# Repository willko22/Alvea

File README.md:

# ⬡ Alvea

**Wireless split keyboard · nRF52840 · ZMK · hexagonal keycaps**

A low-power, battery-powered wireless split keyboard. Each half is a fully independent BLE device with its own battery, per-key LEDs, and USB-C charging.

> [!WARNING]
> **Work in progress — nothing here has been fabricated or tested yet.**
> The hardware is fully designed, but the boards haven't been manufactured, assembled, or brought up. Any performance numbers are design targets, not measurements, and the firmware doesn't exist yet. This repo is documentation of my hobby build, not a guide for replicating it.

---

## 🗺️ Roadmap

| Stage | Status |
|-------|--------|
| Schematic design | ✅ Done |
| PCB layout | ✅ Done |
| BOM finalized | ✅ Done |
| **PCB polishing + panelization** | 🔄 **In progress** |
| PCB fabrication (JLCPCB) | ⬜ Planned |
| SMT assembly | ⬜ Planned |
| Hand-soldering (sockets, LEDs, battery lead) | ⬜ Planned |
| Bootloader flashing (SWD, one-time) | ⬜ Planned |
| ZMK firmware (keymap + board definition) | ⬜ Not started |
| Bring-up & testing | ⬜ Planned |
| 3D-printed case | ⬜ Planned (after electronics work) |
| Renders / photos | ⬜ Not yet available |

**Right now:** finishing the PCBs and panelizing for fabrication.
**After that:** fabrication → SMT assembly → hand-soldering → firmware → testing → case design.

Legend: ✅ done · 🔄 in progress · ⬜ planned / not started

---

## ✨ Highlights

- **Wireless BLE** — each half is fully independent; no TRRS cable between halves
- **nRF52840 module (Ebyte E73-2G4M08S1C)** — integrated PCB antenna, so no RF design needed
- **ZMK firmware** *(planned)* — flexible keymaps, deep-sleep power management, drag-and-drop USB updates
- **19 functional keys per half** in a 5×4 matrix, plus a dedicated power switch
- **Per-key LEDs** shining up through translucent hexagonal HEX keycaps
- **USB-C charging** with a dedicated fuel gauge for accurate battery reporting
- **Single 3.5 Ah LiPo per half** with ZMK deep sleep — see [`DESIGN.md`](DESIGN.md) for the per-component power breakdown

Full technical detail — every component, net, pin assignment, BOM line, the power/charging architecture, and the design rationale — lives in [`DESIGN.md`](DESIGN.md).

---

## 🛒 Sourcing

| Source | Parts |
|--------|-------|
| [JLCPCB](https://jlcpcb.com/) | PCB fabrication + SMT assembly of the small components |
| [Keeb Supply](https://keeb.supply/) | Twilight low-profile switches, HEX keycaps, foam Choc spacers, hotswap Choc sockets, battery connector |
| [TME](https://www.tme.eu/) | Per-key LEDs, battery, and a Raspberry Pi Pico (firmware burner + SWD debugger) |

The switches are **not soldered** — only the hotswap Choc sockets are, and the switches snap into those.

---

## 📄 License

This repository is **split-licensed**:

- **Hardware design files & documentation** — [CC BY-NC 4.0](https://creativecommons.org/licenses/by-nc/4.0/). Use, share, and modify freely with credit, but **not for commercial purposes** — no one may sell Alvea or its derivatives without my explicit consent. See [`LICENSE`](LICENSE).
- **Firmware** (ZMK keymap / board definition) — [MIT](https://opensource.org/licenses/MIT), matching [ZMK](https://zmk.dev/)'s own license so it stays compatible with the ZMK ecosystem. See [`LICENSE-FIRMWARE`](LICENSE-FIRMWARE).

The non-commercial restriction protects the hardware — the part someone would actually manufacture. The firmware is a thin config on top of MIT-licensed ZMK, so it matches ZMK.

---

## 🙏 Acknowledgements

- [ZMK Firmware](https://zmk.dev/)
- [Adafruit nRF52 Bootloader](https://github.com/adafruit/Adafruit_nRF52_Bootloader)
- [fkcaps HEX keycaps](https://fkcaps.com/keycaps/hex) by *s-ol*
- The KiCad community for guidance

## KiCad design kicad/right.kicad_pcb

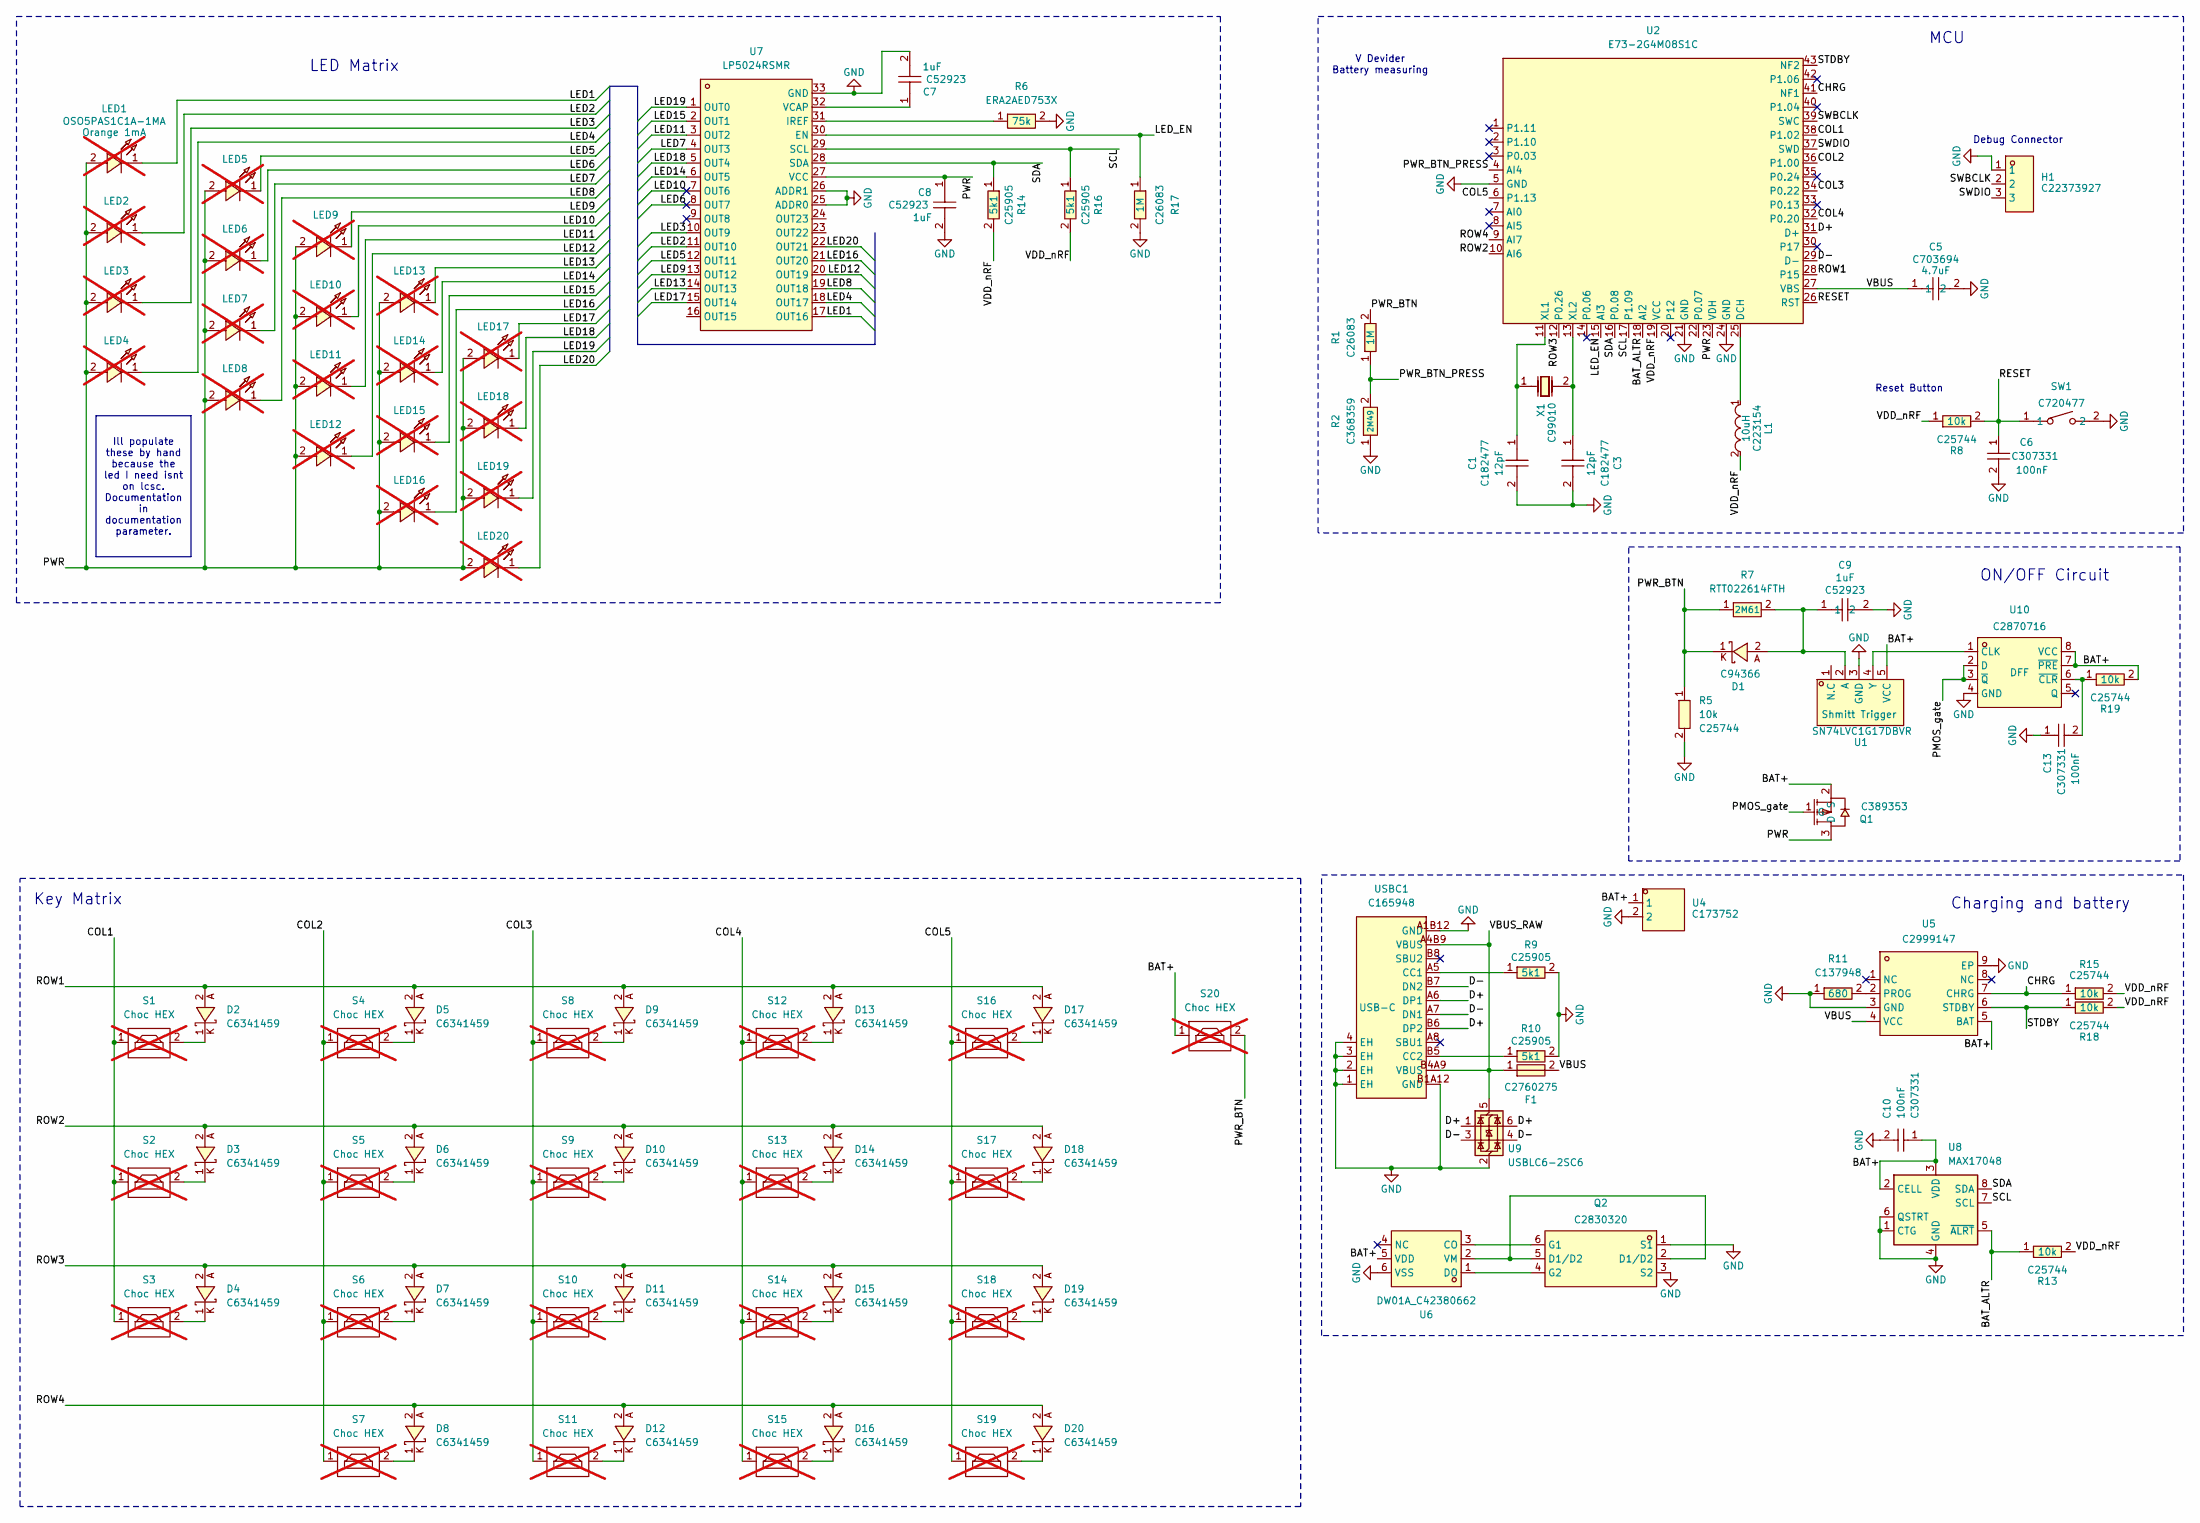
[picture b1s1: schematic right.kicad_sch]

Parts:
C1, C3: 0402CG120F500NT; C0402; LCSC Part C182477
C5: ZRB15XR61A475KE01D; C0402; MPN ZRB15XR61A475KE01D; LCSC Part C703694
C6, C10, C13: CL05B104KB54PNC; C0402; LCSC Part C307331
C7, C8, C9: CL05A105KA5NQNC; C0402; LCSC Part C52923
D1: NSR05F20NXT5G; DSN2_L1.0-W0.6-RD; LCSC Part C94366
D2, D3, D4, D5, D6, D7, D8, D9, D10, D11, D12, D13, D14, D15, D16, D17, D18, D19, D20: CDSQC4148-HF; X1-DFN1006-2_L1.0-W0.6-RD; LCSC Part C6341459
F1: SMD1206-150C-16V; F1206; LCSC Part C2760275
H1: HC-PM254-8.5H-1X3PW; HDR-TH_3P-P2.54_HC-PM254-8.5H-1X3PW; LCSC Part C22373927
L1: BRC2016T100K; IND-SMD_L2.0-W1.6_BRC2016; LCSC Part C223154
LED1, LED2, LED3, LED4, LED5, LED6, LED7, LED8, LED9, LED10, LED11, LED12, LED13, LED14, LED15, LED16, LED17, LED18, LED19, LED20: OSO5PAS1C1A-1MA; LED-SMD_L3.2-W2.8-LS3.5-RD-BLUE; LCSC Part OSO5PAS1C1A-1MA -> on tme.ue; not fitted
Q1: PMF170XP,115; SOT-323-3_L2.0-W1.3-P1.30-LS2.1-BR; LCSC Part C389353
Q2: FS8205A_C2830320; SOT-23-6_L2.9-W1.6-P0.95-LS2.8-BR; LCSC Part C2830320
R1, R17: 0402WGF1004TCE; R0402; LCSC Part C26083
R2: WR04W2494FTL; R0402; LCSC Part C368359
R5, R8, R13, R15, R18, R19: 0402WGF1002TCE; R0402; LCSC Part C25744
R6: ERA2AED753X; R0402; MPN ERA2AED753X; LCSC Part C491105
R7: RTT022614FTH; R0402; MPN RTT022614FTH; LCSC Part C166493
R9, R10, R14, R16: 0402WGF5101TCE; R0402; LCSC Part C25905
R11: RC0402FR-07680RL; R0402; LCSC Part C137948
S1, S2, S3, S4, S5, S6, S7, S8, S9, S10, S11, S12, S13, S14, S15, S16, S17, S18, S19, S20: Choc HEX; PG1350_hotswap; not fitted
SW1: TS-1088-AR02016; SW-SMD_L3.9-W3.0-P4.45; LCSC Part C720477
U1: SN74LVC1G17DBVR; SOT-23-5_L3.0-W1.7-P0.95-LS2.8-BR; MPN SN74LVC1G17DBVR; LCSC Part C7836
U2: E73-2G4M08S1C; WIRELM-SMD_E73-2G4M08S1C; LCSC Part C356849
U4: S2B-PH-K-S(LF)(SN); CONN-TH_S2B-PH-K-S-LF-SN; LCSC Part C173752
U5: BL8573CS8TR; ESOP-8_L4.9-W3.9-P1.27-LS6.0-BL-EP; LCSC Part C2999147
U6: DW01A_C42380662; SOT-23-6_L2.9-W1.6-P0.95-LS2.9-BL; LCSC Part C42380662
U7: LP5024RSMR; VQFN-32_L4.0-W4.0-P0.40-TL-EP; LCSC Part C427525
U8: MAX17048; DFN-8_2x2mm_P0.5mm_EP1.2x0.8mm; LCSC Part C2682616
U9: USBLC6-2SC6; SOT-23-6
U10: SN74LVC1G74DQER; X2SON-8_L1.4-W1.0-P0.35-BL; LCSC Part C2870716
USBC1: TYPE-C-31-M-12; USB-C_SMD-TYPE-C-31-M-12_1; LCSC Part C165948
X1: FC-13532.768KHZ9PF20PPM; OSC-SMD_L3.2-W1.5; LCSC Part C99010

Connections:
/BAT+: C10.1, Q1.2 (S), R19.2, S20.1, U1.5 (VCC), U4.1, U5.5 (BAT), U6.5 (VDD), U8.2 (CELL), U8.3 (VDD), U10.7 (~PRE), U10.8 (VCC); also elsewhere on the board
/BAT_ALTR: R13.1, U2.18 (AI2), U8.5 (~ALRT)
/CHRG: R15.1, U2.41 (NF1), U5.7 (CHRG)
/COL1: S1.1, S2.1, S3.1, U2.38 (P1.02)
/COL2: S4.1, S5.1, S6.1, S7.1, U2.36 (P1.00)
/COL3: S8.1, S9.1, S10.1, S11.1, U2.34 (P0.22)
/COL4: S12.1, S13.1, S14.1, S15.1, U2.32 (P0.20)
/COL5: S16.1, S17.1, S18.1, S19.1, U2.6 (P1.13)
/D+: U2.31 (D+), U9.1 (I/O1), U9.6 (I/O1), USBC1.A6 (DP1), USBC1.B6 (DP2)
/D-: U2.29 (D-), U9.3 (I/O2), U9.4 (I/O2), USBC1.A7 (DN1), USBC1.B7 (DN2)
/LED1: LED1.1, U7.17 (OUT16)
/LED2: LED2.1, U7.11 (OUT10)
/LED3: LED3.1, U7.10 (OUT9)
/LED4: LED4.1, U7.18 (OUT17)
/LED5: LED5.1, U7.12 (OUT11)
/LED6: LED6.1, U7.8 (OUT7)
/LED7: LED7.1, U7.4 (OUT3)
/LED8: LED8.1, U7.19 (OUT18)
/LED9: LED9.1, U7.13 (OUT12)
/LED10: LED10.1, U7.7 (OUT6)
/LED11: LED11.1, U7.3 (OUT2)
/LED12: LED12.1, U7.20 (OUT19)
/LED13: LED13.1, U7.14 (OUT13)
/LED14: LED14.1, U7.6 (OUT5)
/LED15: LED15.1, U7.2 (OUT1)
/LED16: LED16.1, U7.21 (OUT20)
/LED17: LED17.1, U7.15 (OUT14)
/LED18: LED18.1, U7.5 (OUT4)
/LED19: LED19.1, U7.1 (OUT0)
/LED20: LED20.1, U7.22 (OUT21)
/LED_EN: R17.1, U2.15 (AI3), U7.30 (EN)
/PMOS_gate: Q1.1 (G), U10.2 (D), U10.3 (~Q)
/PWR: C8.1, LED1.2, LED2.2, LED3.2, LED4.2, LED5.2, LED6.2, LED7.2, LED8.2, LED9.2, LED10.2, LED11.2, LED12.2, LED13.2, LED14.2, LED15.2, LED16.2, LED17.2, LED18.2, LED19.2, LED20.2, Q1.3 (D), U2.23 (VDH), U7.27 (VCC); also elsewhere on the board
/PWR_BTN: D1.1, R1.2, R5.1, R7.1, S20.2
/PWR_BTN_PRESS: R1.1, R2.2, U2.4 (AI4)
/RESET: C6.1, R8.2, SW1.1, U2.26 (RST)
/ROW1: D2.2, D5.2, D9.2, D13.2, D17.2, U2.28 (P15)
/ROW2: D3.2, D6.2, D10.2, D14.2, D18.2, U2.10 (AI6)
/ROW3: D4.2, D7.2, D11.2, D15.2, D19.2, U2.12 (P0.26)
/ROW4: D8.2, D12.2, D16.2, D20.2, U2.9 (AI7)
/SCL: R16.1, U2.17 (P1.09), U7.29 (SCL), U8.7 (SCL)
/SDA: R14.1, U2.16 (P0.08), U7.28 (SDA), U8.8 (SDA)
/STDBY: R18.1, U2.43 (NF2), U5.6 (STDBY)
/SWBCLK: H1.2, U2.39 (SWC)
/SWDIO: H1.3, U2.37 (SWD)
/VBUS: C5.1, F1.2, U2.27 (VBS), U5.4 (VCC); also elsewhere on the board
/VBUS_RAW: F1.1, U9.5 (VBUS), USBC1.A4B9 (VBUS), USBC1.B4A9 (VBUS)
/VDD_nRF: L1.2, R8.1, R13.2, R14.2, R15.2, R16.2, R18.2, U2.19 (VCC); also elsewhere on the board
GND: C1.2, C3.2, C5.2, C6.2, C7.2, C8.2, C9.2, C10.2, C13.1, H1.1, Q2.1 (S1), Q2.3 (S2), R2.1, R5.2, R6.2, R9.2, R10.2, R11.1, R17.2, SW1.2, U1.3 (GND), U2.5 (GND), U2.21 (GND), U2.24 (GND), U4.2, U5.3 (GND), U5.9 (EP), U6.6 (VSS), U7.25 (ADDR0), U7.26 (ADDR1), U7.33 (GND), U8.1 (CTG), U8.4 (GND), U8.6 (QSTRT), U8.9 (GND), U9.2 (GND), U10.4 (GND), USBC1.1 (EH), USBC1.2 (EH), USBC1.3 (EH), USBC1.4 (EH), USBC1.A1B12 (GND), USBC1.B1A12 (GND); also elsewhere on the board
unnamed: D2.1, S1.2
unnamed: D3.1, S2.2
unnamed: D4.1, S3.2
unnamed: D5.1, S4.2
unnamed: D6.1, S5.2
unnamed: D7.1, S6.2
unnamed: D8.1, S7.2
unnamed: D9.1, S8.2
unnamed: D10.1, S9.2
unnamed: D11.1, S10.2
unnamed: D12.1, S11.2
unnamed: D13.1, S12.2
unnamed: D14.1, S13.2
unnamed: D15.1, S14.2
unnamed: D16.1, S15.2
unnamed: D17.1, S16.2
unnamed: D18.1, S17.2
unnamed: D19.1, S18.2
unnamed: D20.1, S19.2
unnamed: Q2.6 (G1), U6.3 (CO)
unnamed: Q2.4 (G2), U6.1 (DO)
unnamed: C9.1, D1.2, R7.2, U1.2 (A)
unnamed: U1.4 (Y), U10.1 (CLK)
unnamed: L1.1, U2.25 (DCH)
unnamed: C1.1, U2.11 (XL1), X1.1
unnamed: C3.1, U2.13 (XL2), X1.2
unnamed: R11.2, U5.2 (PROG)
unnamed: Q2.2 (D1/D2), Q2.5 (D1/D2), U6.2 (VM)
unnamed: R6.1, U7.31 (IREF)
unnamed: C7.1, U7.32 (VCAP)
unnamed: C13.2, R19.1, U10.6 (~CLR)
unnamed: R9.1, USBC1.A5 (CC1)
unnamed: R10.1, USBC1.B5 (CC2)

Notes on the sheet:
Charging and battery
MCU
Debug Connector
ON/OFF Circuit
Reset Button
Key Matrix
V Devider Battery measuring
LED Matrix
Ill populate these by hand because the led I need isnt on lcsc. Documentation in documentation parameter.

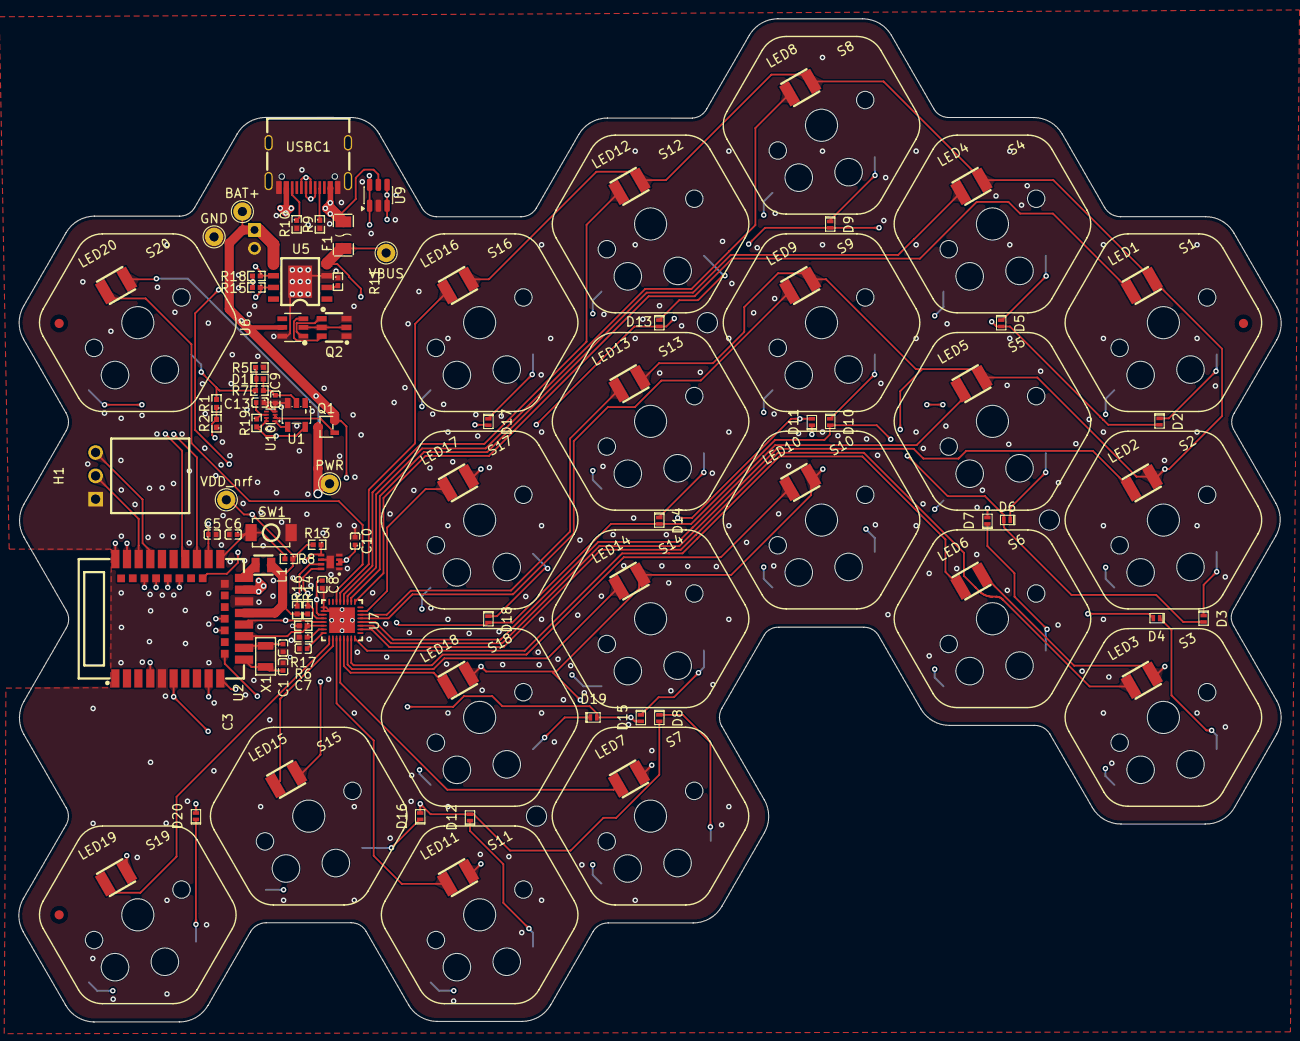
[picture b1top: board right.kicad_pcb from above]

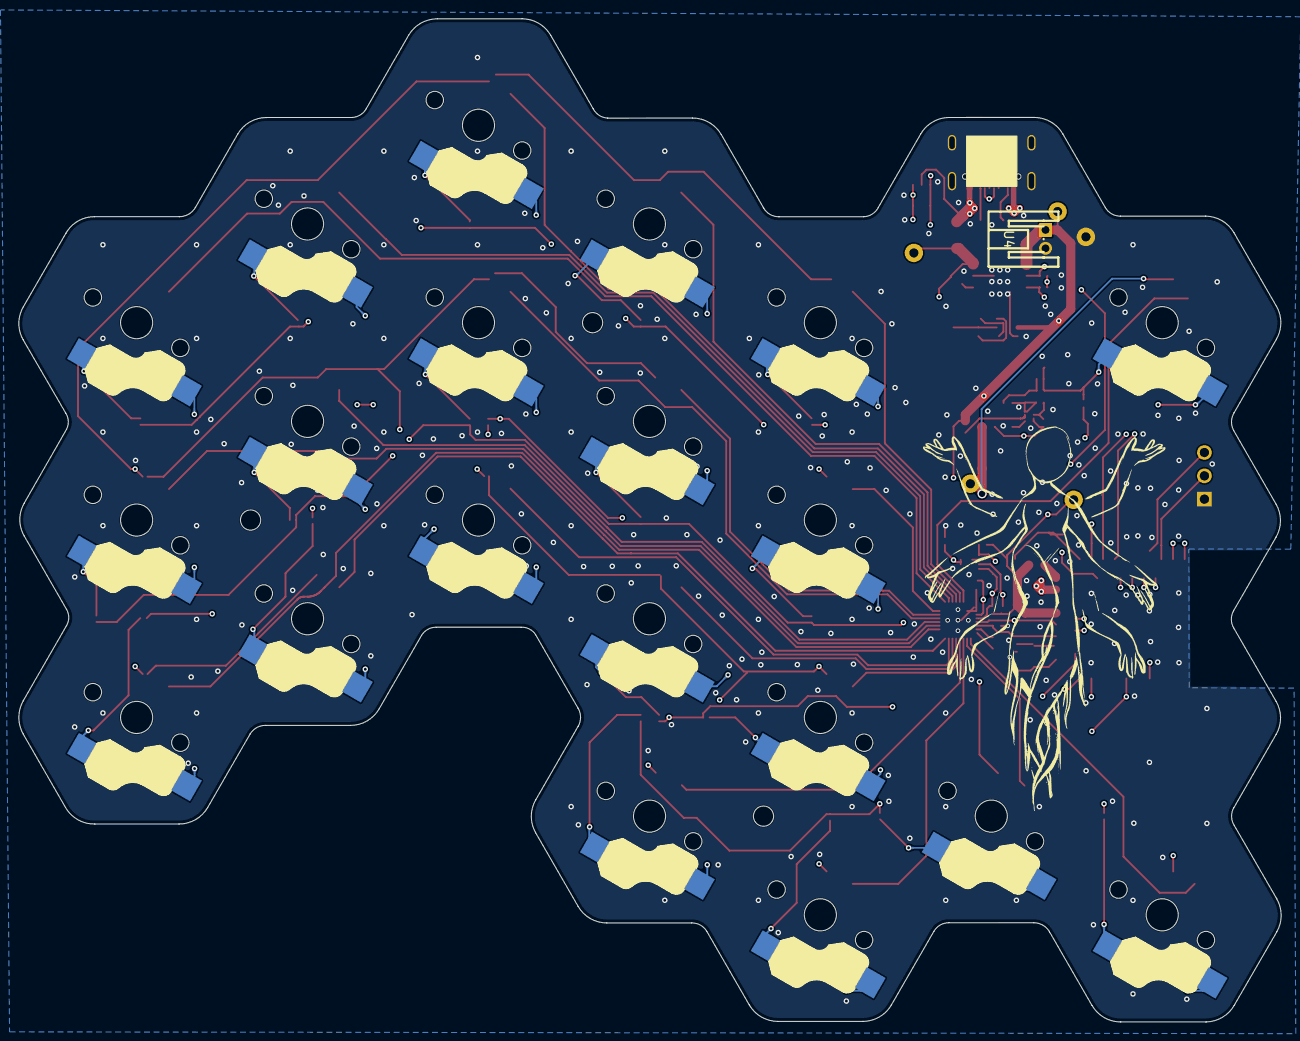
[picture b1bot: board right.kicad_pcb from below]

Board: 4 copper layers, 137.5 x 109.3 mm, 111 parts (22 on the bottom side), 82 nets.

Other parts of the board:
BAT+: TestPoint_THTPad_D2.0mm_Drill1.0mm
Fi4, Fi5: Fiducial_1mm_Mask2mm
Fi6: Fiducial_1mm_Mask2mm
G**: LOGO; handy
GND: TestPoint_THTPad_D2.0mm_Drill1.0mm
PWR: TestPoint_THTPad_D2.0mm_Drill1.0mm
VBUS: TestPoint_THTPad_D2.0mm_Drill1.0mm
VDD_nrf: TestPoint_THTPad_D2.0mm_Drill1.0mm

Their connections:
/BAT+: BAT+.1; also elsewhere on the board
/PWR: PWR.1; also elsewhere on the board
/VBUS: VBUS.1; also elsewhere on the board
/VDD_nRF: VDD_nrf.1; also elsewhere on the board
GND: GND.1; also elsewhere on the board

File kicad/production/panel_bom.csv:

Designator,Footprint,Quantity,Value,LCSC Part #
"C1_2, C3_2",C0402,2,0402CG120J500NT,C1547
"C1, C3",C0402,2,0402CG120F500NT,C182477
"C10, C13, C4, C6_2, C6, C9_2",C0402,6,CL05B104KB54PNC,C307331
"C2, C7_2, C7, C8_2, C8, C9",C0402,6,CL05A105KA5NQNC,C52923
"C5_2, C5",C0402,2,ZRB15XR61A475KE01D,C703694
"D1_2, D1",DSN2_L1.0-W0.6-RD,2,NSR05F20NXT5G,C94366
"D10_2, D10, D11_2, D11, D12_2, D12, D13_2, D13, D14_2, D14, D15_2, D15, D16_2, D16, D17_2, D17, D18_2, D18, D19_2, D19, D2_2, D2, D20_2, D20, D3_2, D3, D4_2, D4, D5_2, D5, D6_2, D6, D7_2, D7, D8_2, D8, D9_2, D9",X1-DFN1006-2_L1.0-W0.6-RD,38,CDSQC4148-HF,C6341459
"F1_2, F1",F1206,2,SMD1206-150C-16V,C2760275
"FI1, FI2, FI3, FI6",,4,Fiducial_1mm_Mask2mm,
H1_2,HDR-TH_3P-P2.54_HC-PM254-8.5H-1X3PW,1,HC-PM254-8.5H-1X3PW,C22373927
L1_2,IND-SMD_L2.0-W1.6_BRC2016,1,BRC2016T100K,C223154
"Q1_2, Q1",SOT-323-3_L2.0-W1.3-P1.30-LS2.1-BR,2,"PMF170XP,115",C389353
"Q2_2, Q2",SOT-23-6_L2.9-W1.6-P0.95-LS2.8-BR,2,FS8205A_C2830320,C2830320
"R1_2, R1, R17_2, R17",R0402,4,0402WGF1004TCE,C26083
"R10_2, R10, R14_2, R14, R16_2, R16, R9_2, R9",R0402,8,0402WGF5101TCE,C25905
"R11_2, R11",R0402,2,RC0402FR-07680RL,C137948
"R12, R13_2, R13, R15, R18, R19, R3, R4, R5, R7_2, R8_2, R8",R0402,12,0402WGF1002TCE,C25744
"R2_2, R2",R0402,2,WR04W2494FTL,C368359
"R5_2, R7",R0402,2,RTT022614FTH,C166493
"R6_2, R6",R0402,2,ERA2AED753X,C491105
"SW1_2, SW1",SW-SMD_L3.9-W3.0-P4.45,2,TS-1088-AR02016,C720477
"U1_2, U1",SOT-23-5_L3.0-W1.7-P0.95-LS2.8-BR,2,SN74LVC1G17DBVR,C7836
U10,X2SON-8_L1.4-W1.0-P0.35-BL,1,SN74LVC1G74DQER,C2870716
U2_2,WIRELM-SMD_E73-2G4M08S1C,1,E73-2G4M08S1C,C356849
U4_2,CONN-TH_S2B-PH-K-S-LF-SN,1,S2B-PH-K-S(LF)(SN),C173752
"U5_2, U5",ESOP-8_L4.9-W3.9-P1.27-LS6.0-BL-EP,2,BL8573CS8TR,C2999147
U6_2,SOT-23-6_L2.9-W1.6-P0.95-LS2.9-BL,1,DW01A_C42380662,C42380662
U7_2,VQFN-32_L4.0-W4.0-P0.40-TL-EP,1,LP5024RSMR,C427525
"U8_2, U8",DFN-8_2x2mm_P0.5mm_EP1.2x0.8mm,2,MAX17048,C2682616
"U9_2, U9",SOT-23-6,2,USBLC6-2SC6,
"USBC1_2, USBC1",USB-C_SMD-TYPE-C-31-M-12_1,2,TYPE-C-31-M-12,C165948
"X1_2, X1",OSC-SMD_L3.2-W1.5,2,FC-13532.768KHZ9PF20PPM,C99010

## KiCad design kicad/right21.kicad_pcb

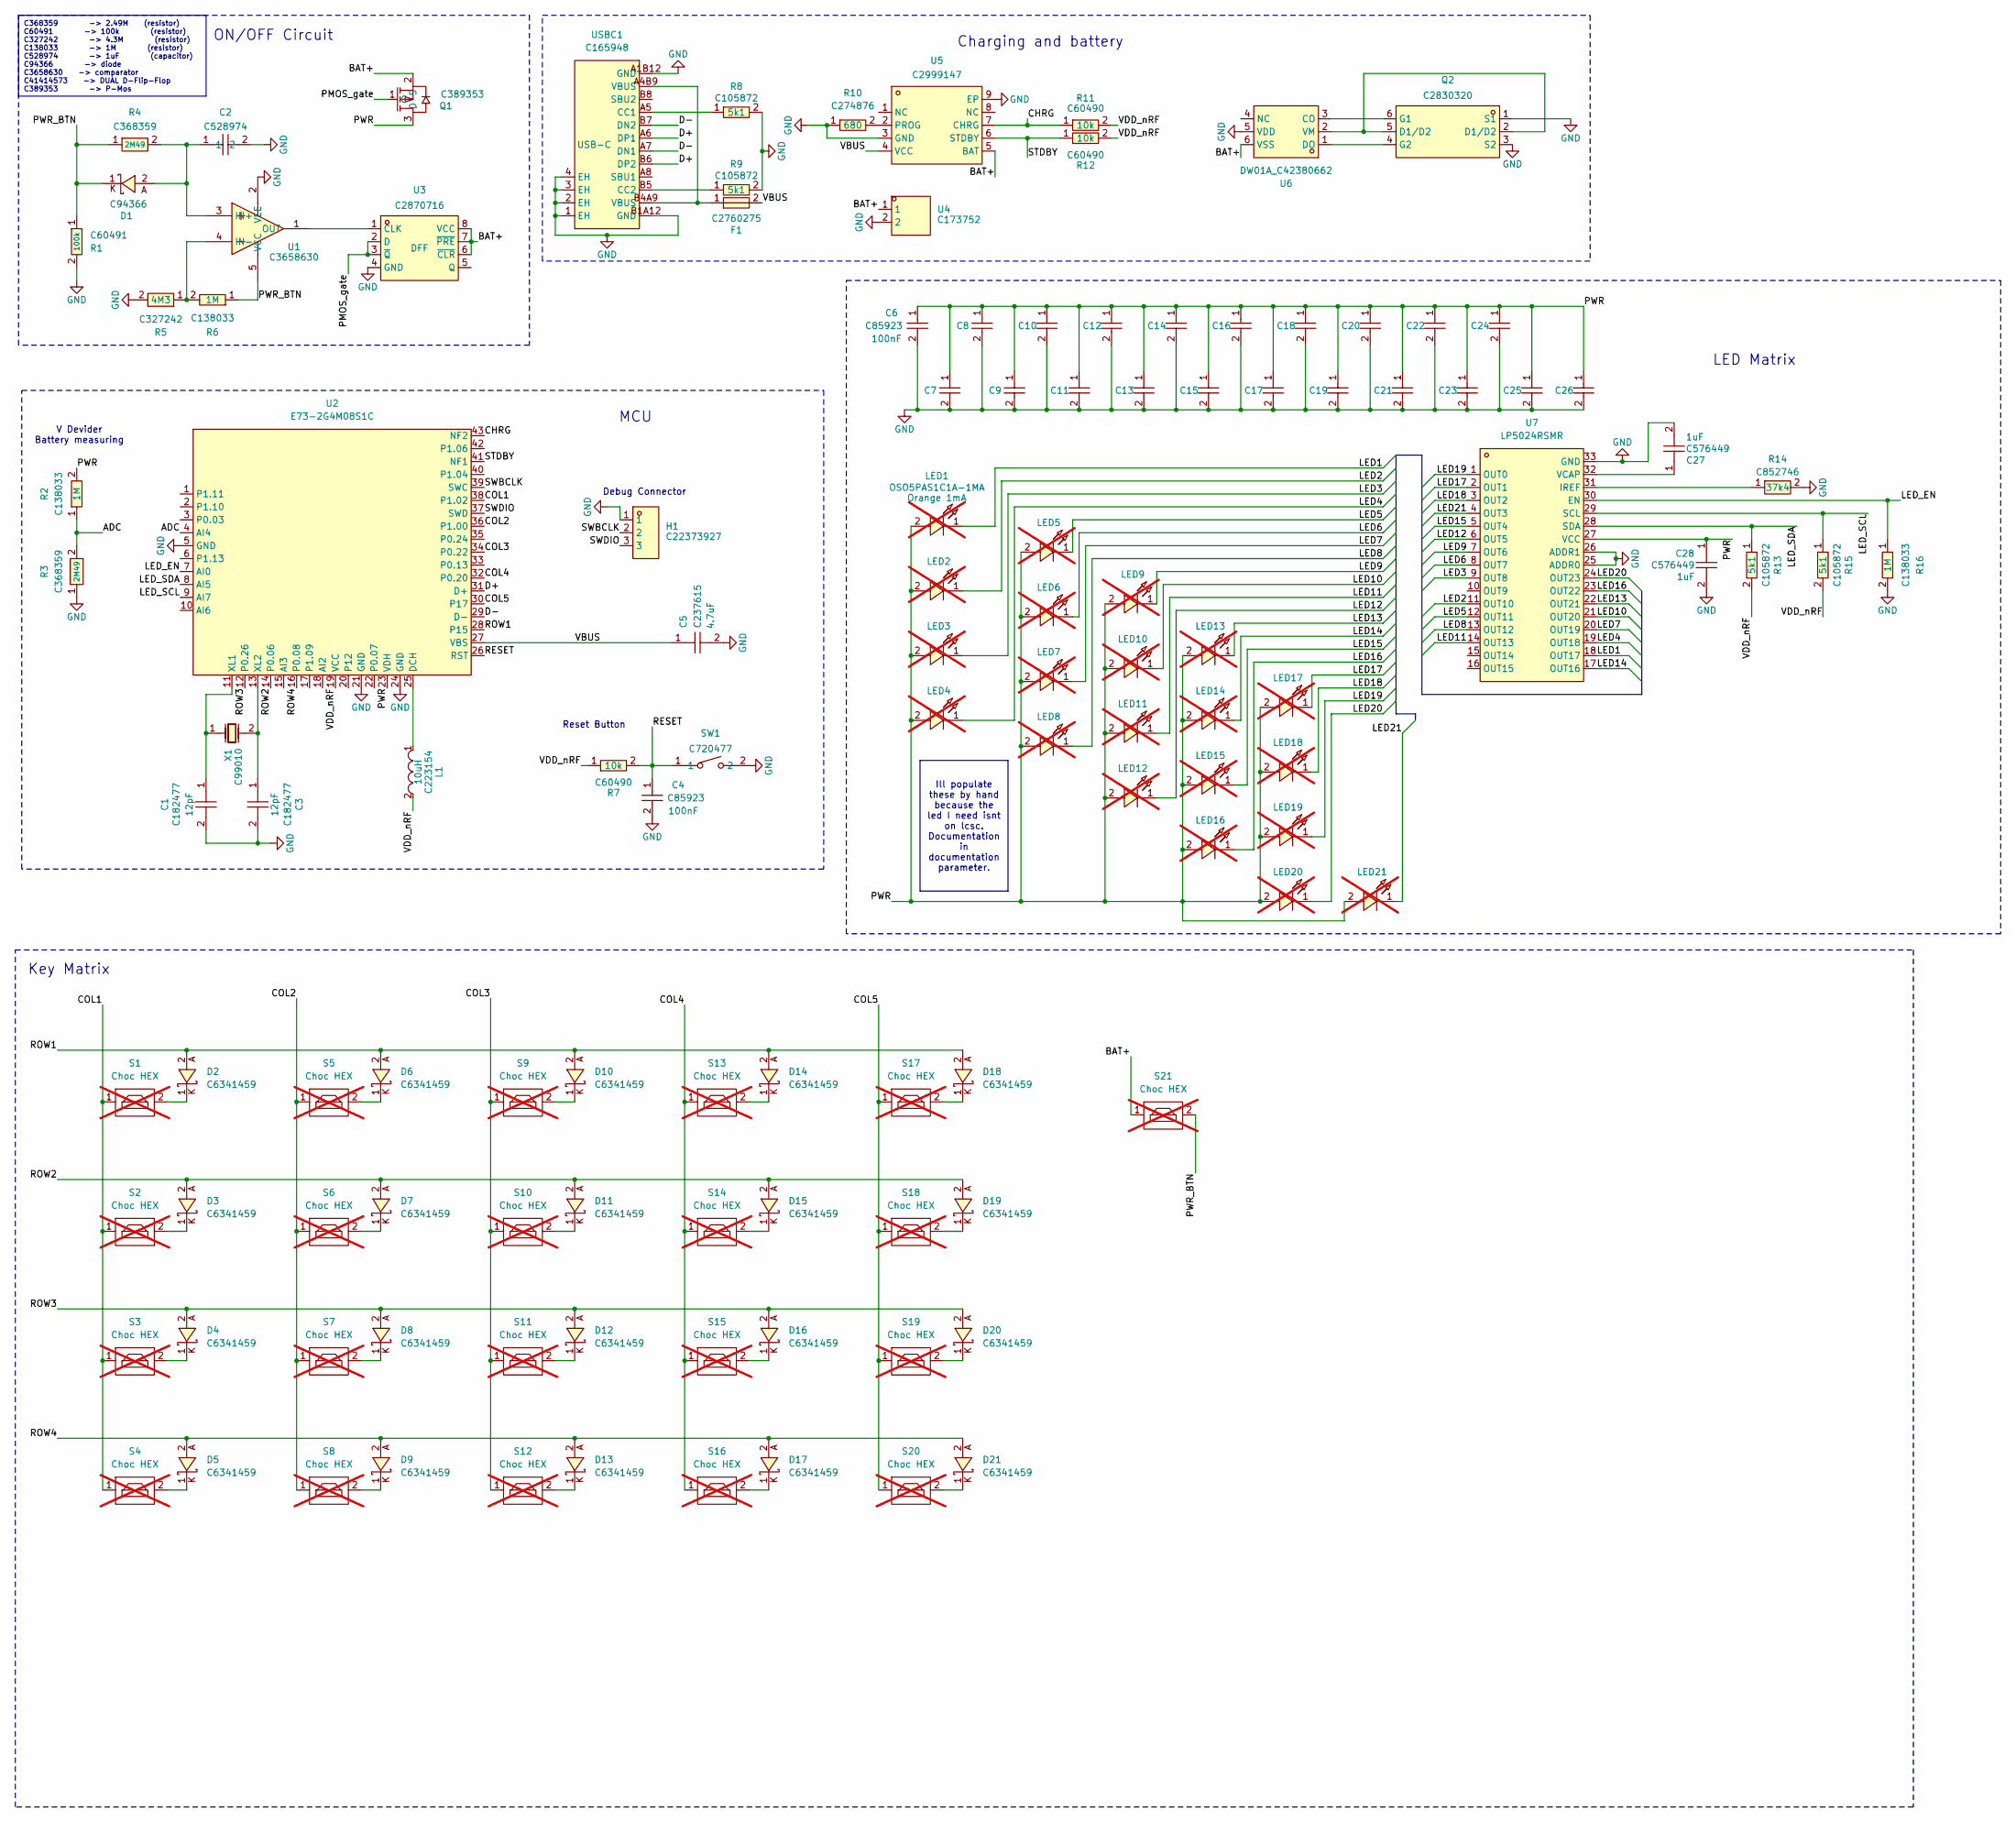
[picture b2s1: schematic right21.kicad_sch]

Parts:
C1, C3: 0402CG120F500NT; C0402; LCSC Part C182477
C2: GRM155Z71A105KE01D; C0402; LCSC Part C528974
C4, C6, C7, C8, C9, C10, C11, C12, C13, C14, C15, C16, C17, C18, C19, C20, C21, C22, C23, C24, C25, C26: GRM033C71C104KE14D; C0201; LCSC Part C85923
C5: GRM188C71C475KE21D; C0603; LCSC Part C237615
C27, C28: GRM155C71C105KE11D; C0402; LCSC Part C576449
D1: NSR05F20NXT5G; DSN2_L1.0-W0.6-RD; LCSC Part C94366
D2, D3, D4, D5, D6, D7, D8, D9, D10, D11, D12, D13, D14, D15, D16, D17, D18, D19, D20, D21: CDSQC4148-HF; X1-DFN1006-2_L1.0-W0.6-RD; LCSC Part C6341459
F1: SMD1206-150C-16V; F1206; LCSC Part C2760275
H1: HC-PM254-8.5H-1X3PW; HDR-TH_3P-P2.54_HC-PM254-8.5H-1X3PW; LCSC Part C22373927
L1: BRC2016T100K; IND-SMD_L2.0-W1.6_BRC2016; LCSC Part C223154
LED1, LED2, LED3, LED4, LED5, LED6, LED7, LED8, LED9, LED10, LED11, LED12, LED13, LED14, LED15, LED16, LED17, LED18, LED19, LED20, LED21: OSO5PAS1C1A-1MA; LED-SMD_L3.2-W2.8-LS3.5-RD-BLUE; LCSC Part OSO5PAS1C1A-1MA -> on tme.ue; not fitted
Q1: PMF170XP,115; SOT-323-3_L2.0-W1.3-P1.30-LS2.1-BR; LCSC Part C389353
Q2: FS8205A_C2830320; SOT-23-6_L2.9-W1.6-P0.95-LS2.8-BR; LCSC Part C2830320
R1: RC0402FR-07100KL; R0402; LCSC Part C60491
R2, R6, R16: RC0402FR-071ML; R0402; LCSC Part C138033
R3, R4: WR04W2494FTL; R0402; LCSC Part C368359
R5: RC0402FR-074M3L; R0402; LCSC Part C327242
R7, R11, R12: RC0402FR-0710KL; R0402; LCSC Part C60490
R8, R9, R13, R15: RC0402FR-075K1L; R0402; LCSC Part C105872
R10: RC0201FR-07680RL; R0201; LCSC Part C274876
R14: RT0402BRD0737K4L; R0402; LCSC Part C852746
S1, S2, S3, S4, S5, S6, S7, S8, S9, S10, S11, S12, S13, S14, S15, S16, S17, S18, S19, S20, S21: Choc HEX; PG1350_hotswap; not fitted
SW1: TS-1088-AR02016; SW-SMD_L3.9-W3.0-P4.45; LCSC Part C720477
U1: TLV7031QDCKRQ1; SC-70-5_L2.0-W1.3-P0.65-LS2.1-BR; LCSC Part C3658630
U2: E73-2G4M08S1C; WIRELM-SMD_E73-2G4M08S1C; LCSC Part C356849
U3: SN74LVC1G74DQER; X2SON-8_L1.4-W1.0-P0.35-BL; LCSC Part C2870716
U4: S2B-PH-K-S(LF)(SN); CONN-TH_S2B-PH-K-S-LF-SN; LCSC Part C173752
U5: BL8573CS8TR; ESOP-8_L4.9-W3.9-P1.27-LS6.0-BL-EP; LCSC Part C2999147
U6: DW01A_C42380662; SOT-23-6_L2.9-W1.6-P0.95-LS2.9-BL; LCSC Part C42380662
U7: LP5024RSMR; VQFN-32_L4.0-W4.0-P0.40-TL-EP; LCSC Part C427525
USBC1: TYPE-C-31-M-12; USB-C_SMD-TYPE-C-31-M-12_1; LCSC Part C165948
X1: FC-13532.768KHZ9PF20PPM; OSC-SMD_L3.2-W1.5; LCSC Part C99010

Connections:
/ADC: R2.1, R3.2, U2.4 (AI4)
/BAT+: Q1.2 (S), S21.1, U3.6 (~CLR), U3.7 (~PRE), U3.8 (VCC), U4.1, U4.5 (BAT), U5.5 (BAT), U6.6 (VSS); also elsewhere on the board
/CHRG: R11.1, U2.43 (NF2), U4.7 (CHRG), U5.7 (CHRG)
/COL1: S1.1, S2.1, S3.1, S4.1, U2.38 (P1.02)
/COL2: S5.1, S6.1, S7.1, S8.1, U2.36 (P1.00)
/COL3: S9.1, S10.1, S11.1, S12.1, U2.34 (P0.22)
/COL4: S13.1, S14.1, S15.1, S16.1, U2.32 (P0.20)
/COL5: S17.1, S18.1, S19.1, S20.1, U2.30 (P17)
/D+: U2.31 (D+), USBC1.A6 (DP1), USBC1.B6 (DP2)
/D-: U2.29 (D-), USBC1.A7 (DN1), USBC1.B7 (DN2)
/LED1: LED1.1, U7.18 (OUT17)
/LED2: LED2.1, U7.11 (OUT10)
/LED3: LED3.1, U7.9 (OUT8)
/LED4: LED4.1, U7.19 (OUT18)
/LED5: LED5.1, U7.12 (OUT11)
/LED6: LED6.1, U7.8 (OUT7)
/LED7: LED7.1, U7.20 (OUT19)
/LED8: LED8.1, U7.13 (OUT12)
/LED9: LED9.1, U7.7 (OUT6)
/LED10: LED10.1, U7.21 (OUT20)
/LED11: LED11.1, U7.14 (OUT13)
/LED12: LED12.1, U7.6 (OUT5)
/LED13: LED13.1, U7.22 (OUT21)
/LED14: LED14.1, U7.17 (OUT16)
/LED15: LED15.1, U7.5 (OUT4)
/LED16: LED16.1, U7.23 (OUT22)
/LED17: LED17.1, U7.2 (OUT1)
/LED18: LED18.1, U7.3 (OUT2)
/LED19: LED19.1, U7.1 (OUT0)
/LED20: LED20.1, U7.24 (OUT23)
/LED21: LED21.1, U7.4 (OUT3)
/LED_EN: R16.1, U2.7 (AI0), U7.30 (EN)
/LED_SCL: R15.1, U2.9 (AI7), U7.29 (SCL)
/LED_SDA: R13.1, U2.8 (AI5), U7.28 (SDA)
/PMOS_gate: Q1.1 (G), U3.2 (D), U3.3 (~Q)
/PWR: C6.1, C7.1, C8.1, C9.1, C10.1, C11.1, C12.1, C13.1, C14.1, C15.1, C16.1, C17.1, C18.1, C19.1, C20.1, C21.1, C22.1, C23.1, C24.1, C25.1, C26.1, C28.1, LED1.2, LED2.2, LED3.2, LED4.2, LED5.2, LED6.2, LED7.2, LED8.2, LED9.2, LED10.2, LED11.2, LED12.2, LED13.2, LED14.2, LED15.2, LED16.2, LED17.2, LED18.2, LED19.2, LED20.2, LED21.2, Q1.3 (D), R2.2, U2.23 (VDH), U7.27 (VCC)
/PWR_BTN: D1.1, R1.1, R4.1, R6.1, S21.2, U1.5 (VCC)
/RESET: C4.1, R7.2, SW1.1, U2.26 (RST)
/ROW3: D4.2, D8.2, D12.2, D16.2, D20.2, U2.12 (P0.26); also elsewhere on the board
/ROW4: D5.2, D9.2, D13.2, D17.2, D21.2, U2.16 (P0.08)
/STDBY: R12.1, U2.41 (NF1), U4.6 (STDBY), U5.6 (STDBY)
/SWBCLK: H1.2, U2.39 (SWC)
/SWDIO: H1.3, U2.37 (SWD)
/VBUS: C5.1, F1.2, U2.27 (VBS), U4.4 (VCC), U5.4 (VCC)
/VDD_nRF: L1.2, R7.1, R11.2, R12.2, R13.2, R15.2, U2.19 (VCC)
unnamed: D2.1, S1.2
unnamed: D3.1, S2.2
unnamed: D4.1, S3.2
unnamed: D5.1, S4.2
unnamed: D6.1, S5.2
unnamed: D7.1, S6.2
unnamed: D8.1, S7.2
unnamed: D9.1, S8.2
unnamed: D10.1, S9.2
unnamed: D11.1, S10.2
unnamed: D12.1, S11.2
unnamed: D13.1, S12.2
unnamed: D14.1, S13.2
unnamed: D15.1, S14.2
unnamed: D16.1, S15.2
unnamed 62: D17.1, S16.2; also elsewhere on the board
unnamed 63: D18.1, S17.2; also elsewhere on the board
unnamed 64: D19.1, S18.2; also elsewhere on the board
unnamed 65: D20.1, S19.2; also elsewhere on the board
unnamed: D21.1, S20.2
unnamed: F1.1, USBC1.A4B9 (VBUS), USBC1.B4A9 (VBUS)
unnamed 68: Q2.6 (G1), U6.3 (CO); also elsewhere on the board
unnamed 69: Q2.4 (G2), U6.1 (DO); also elsewhere on the board
unnamed: C2.1, D1.2, R4.2, U1.3 (IN+)
unnamed: R5.1, R6.2, U1.4 (IN-)
unnamed: U1.1 (OUT), U3.1 (CLK)
unnamed: L1.1, U2.25 (DCH)
unnamed: C1.1, U2.11 (XL1), X1.1
unnamed: C3.1, U2.13 (XL2), X1.2
unnamed: R14.1, U7.31 (IREF)
unnamed: C27.1, U7.32 (VCAP)
unnamed 78: Q2.2 (D1/D2), Q2.5 (D1/D2), U6.2 (VM); also elsewhere on the board
unnamed: R8.1, USBC1.A5 (CC1)
unnamed: R9.1, USBC1.B5 (CC2)

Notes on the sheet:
MCU
Debug Connector
Key Matrix
Reset Button
LED Matrix
ON/OFF Circuit
V Devider Battery measuring
Charging and battery
Ill populate these by hand because the led I need isnt on lcsc. Documentation in documentation parameter.
C368359 -> 2.49M (resistor) C60491 -> 100k (resistor) C327242 -> 4.3M (resistor) C138033 -> 1M (resistor) C528974 -> 1uF (capacitor) C94366 -> diode C3658630 -> comparator C41414573 -> DUAL D-Flip-Flop C389353 -> P-Mos

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

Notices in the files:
README.md:
Hardware License
